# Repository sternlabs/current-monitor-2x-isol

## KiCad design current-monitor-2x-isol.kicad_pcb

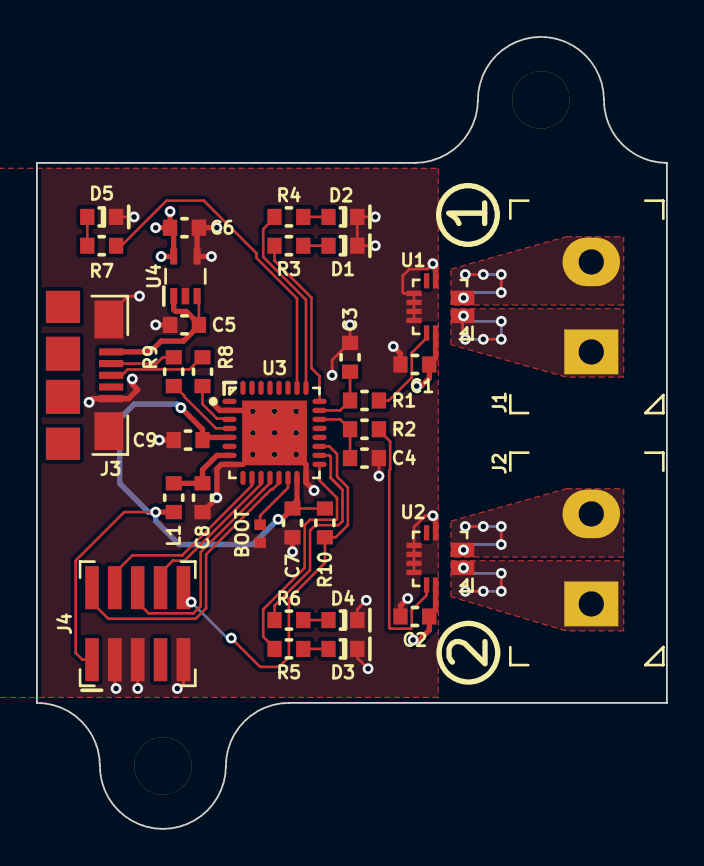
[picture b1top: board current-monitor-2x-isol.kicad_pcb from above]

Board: 2 copper layers, 35.0 x 44.0 mm, 34 parts (0 on the bottom side), 32 nets.

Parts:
C1, C2, C7, C8, C9: 0.1u; SMD-1608
C3, C4: 1n; SMD-1608
C5, C6: 1.0u; SMD-1608
D1, D2, D3, D4, D5: LED; SMD-1608-LED
J1, J2: CONN-2; TERM-2-5.0-8.2-PTH
J3: USB-MICROB; USB-MICRO-B-FCI-10118192
J4: JTAG; CONN-2x5-1.27-SMT
L1: LCORE; SMD-1608
R1, R2: 160k; SMD-1608
R3, R4, R5, R6, R7, R10: 1k; SMD-1608
R8, R9: 33; SMD-1608
SJ1: BOOT; SMD-1005
U1, U2: ACS711EX; acs711ex
U3: MKL27ZxxVFM4
U4: MIC5365; SC-70-5

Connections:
+3V3: C1.1, C2.1, C6.1, C7.1, C9.1, J4.1, L1.1, R10.1, U1.12, U2.12, U3.5, U3.15, U4.5
/BOOT0CFG: SJ1.1, U3.14
/CURRENT1: C3.1, R1.2, U3.23
/CURRENT2: C4.1, R2.2, U3.22
/LED1H: R4.1, U3.25
/LED1L: R3.1, U3.24
/LED2H: R6.1, U3.18
/LED2L: R5.1, U3.17
/LEDACT: R7.1, U3.26
/SWDCLK: J4.4, U3.10
/SWDIO: J4.2, U3.13
/UART_RX: J4.8, U3.11
/UART_TX: J4.6, U3.12
/USBDM: J3.2, R9.1
/USBDP: J3.3, R8.1
/VBUS: C5.1, J3.1, U4.1, U4.3
/~RESET: J4.10, R10.2, U3.19
COM: C1.2, C2.2, C3.2, C4.2, C5.2, C6.2, C7.2, C8.2, C9.2, D1.C, D2.C, D3.C, D4.C, D5.C, J3.5, J3.SHIE, J4.3, J4.5, J4.9, SJ1.2, U1.5, U1.7, U1.8, U1.9, U1.10, U2.5, U2.7, U2.8, U2.9, U2.10, U3.2, U3.8, U3.16, U3.FLAG, U4.2, U4.4
unnamed: C8.1, L1.2, U3.7
unnamed: D1.A, R3.2
unnamed: D2.A, R4.2
unnamed: D3.A, R5.2
unnamed: D4.A, R6.2
unnamed: D5.A, R7.2
unnamed: J1.1, U1.1, U1.2
unnamed: J1.2, U1.3, U1.4
unnamed: J2.1, U2.1, U2.2
unnamed: J2.2, U2.3, U2.4
unnamed: R1.1, U1.11
unnamed: R2.1, U2.11
unnamed: R8.2, U3.3
unnamed: R9.2, U3.4

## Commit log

2015-11-08 initial version
2015-11-09 add mounting lugs
2015-11-09 fix zone layout
2015-11-12 add BOM
2015-11-12 rename from 4x to 2x-isol
2015-11-12 notes, small track change
2015-12-20 use 2.2uF on 3.3V
2015-12-21 small adjustments

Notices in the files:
current-monitor-2x-isol.kicad_pcb:
(c) 2015 Simon Schubert
